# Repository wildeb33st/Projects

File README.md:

# Projects
Repository for Smaller Projects that are not specific to a singular field

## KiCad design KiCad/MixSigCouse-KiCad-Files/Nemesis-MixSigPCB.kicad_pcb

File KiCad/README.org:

* Mixed Signal Hardware Design
This PCB design is based on the course "Mixed Signal Hardware Design" from FEDEVEL Academy. The design makes use of KiCAD for both schematic and PCB Design.  The following URL contains an overview
of the course :
- https://www.phils-lab.net/courses

* Design Specification
Below are the specifications for the design:
- The Device is powered over USB and as such the overall power requirement is *2.5W* with an current of *500mA* and a voltage of *5V*
- The device will be single channel operating within the general audio frequency range i.e. /20Hz to 20kHz/
- Signal Analysis and Signal Generation will be performed by the device
- The use of a DAC/ADC is required along with an MCU. The bit depth chosen for the design is 12.
- The MCU family is the STM32
- SWD is chosen for debugging purposes

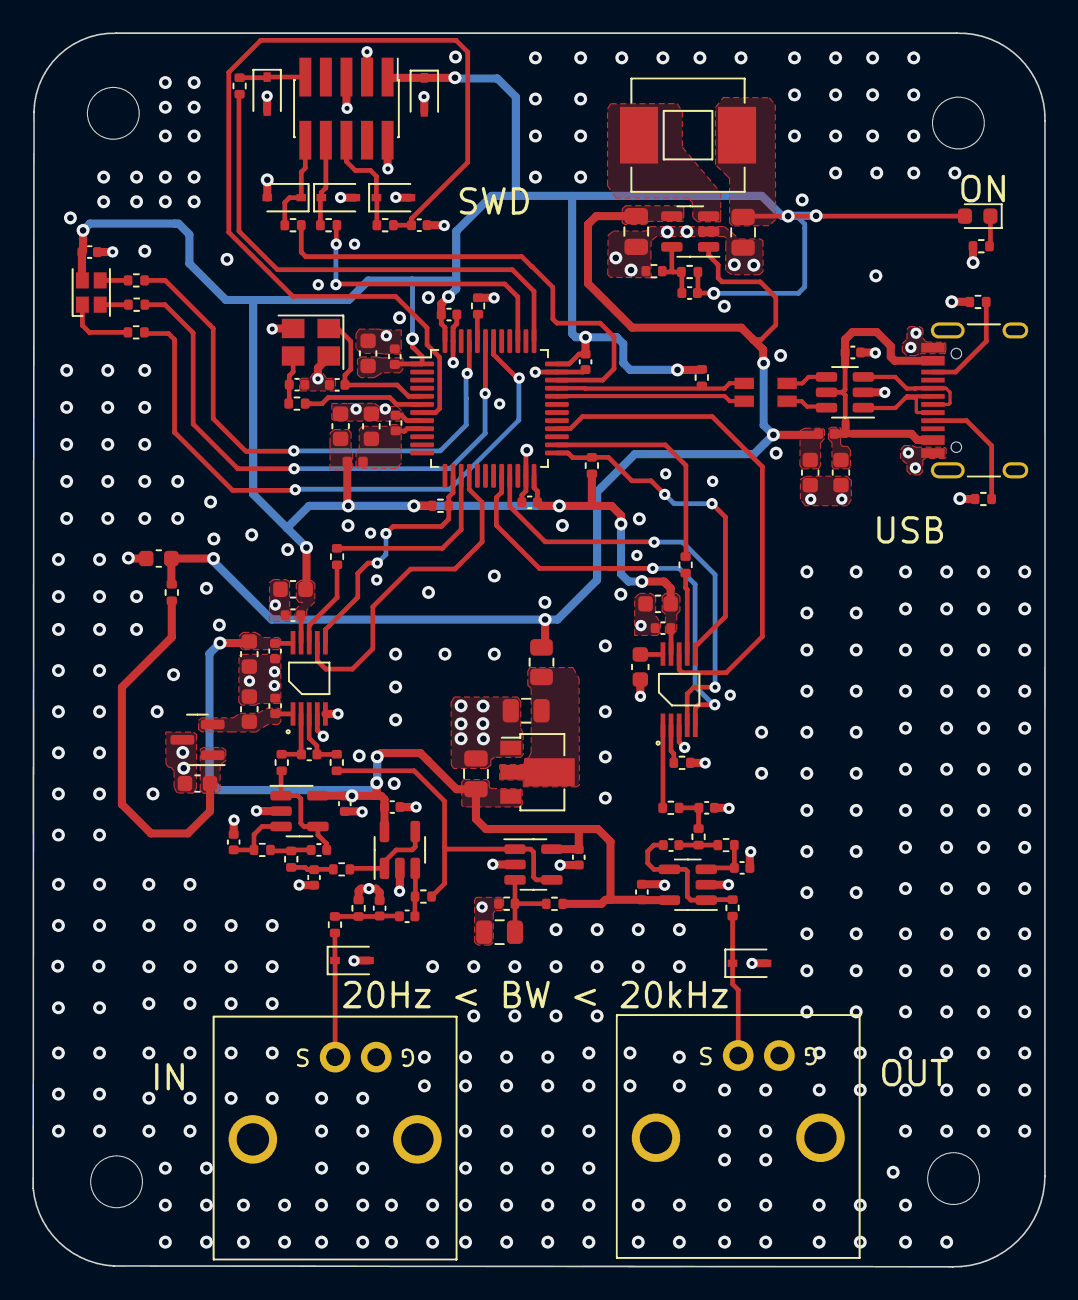
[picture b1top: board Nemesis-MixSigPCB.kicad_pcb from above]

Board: 4 copper layers, 62.5 x 76.2 mm, 114 parts (0 on the bottom side), 68 nets.

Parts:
C100, C101, C206, C207, C402: 1u; C_0603_1608Metric
C102, C103, C104, C105, C107: 22u; C_0805_2012Metric
C106: DNP; C_0402_1005Metric
C108, C201, C202, C203, C204, C210, C211, C212, C301, C302, C306, C311, C313, C314, C401, C406: 100n; C_0402_1005Metric
C200, C308, C309, C310, C312, C315, C400: 10u; C_0603_1608Metric
C205: 10n; C_0402_1005Metric
C208, C209: 10p; C_0402_1005Metric
C300, C304, C307, C404: 150p; C_0402_1005Metric
C303, C305, C403, C405: 1n; C_0402_1005Metric
D100: GREEN; LED_0603_1608Metric
D200: LED_RGB_E6C1206RGBC3UDA; LED_Cree-PLCC4_2x2mm_CW
D201, D202, D203, D204, D205, D300, D400: PESD3V3L1BA,115; D_SOD-323
H1, H2, H3, H4: MountingHole; MountingHole_3.2mm_M3
J200: USB_C_Receptacle_USB2.0; USB_C_Receptacle_HRO_TYPE-C-31-M-12
J201: 2x5 1.27mm; PinHeader_2x05_P1.27mm_Vertical_SMD
J300, J400: 031-5640-1010; AMPHENOL-BNC-031-5640-1010
L100, L200: 10n; L_0402_1005Metric
L101: 15u; MWSA0603S
L201: CMF3216F-900-2P-T; CMC-1206
R100: 10R; R_0805_2012Metric
R101: 100k; R_0402_1005Metric
R102, R304, R403: 22k; R_0402_1005Metric
R103, R104, R105, R207, R208, R209, R300, R306, R307: 1k; R_0402_1005Metric
R200, R202, R203, R401: 10k; R_0402_1005Metric
R201, R309, R400: 0R; R_0402_1005Metric
R204: 1k5; R_0402_1005Metric
R205, R206: 5k1; R_0402_1005Metric
R210, R211, R212, R213, R308, R405: 49R9; R_0402_1005Metric
R301, R302: 2M2; R_0402_1005Metric
R303, R402: 6k8; R_0402_1005Metric
R305, R404: 12k; R_0402_1005Metric
U100: HT7533-1; SOT-89-3
U101: TLV62569DBV; SOT-23-5
U102, U300, U301, U401: MCP6001T-E/OT; SOT-23-5
U200: STM32F103CBT6; LQFP-48_7x7mm_P0.5mm
U201: USBLC6-2SC6; SOT-23-6
U302: REF3033AIDBZT; SOT-23
U303: ADC141S626CIMM_NOPB; VSSOP-10
U400: DAC7563SDGSR; VSSOP-10
Y200: 16MHz; Crystal_SMD_3225-4Pin_3.2x2.5mm

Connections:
+3.3VA: C103.1, C108.1, C302.1, C306.1, C312.1, C313.1, C406.1, R104.2, U100.3 (VOUT), U102.5 (V+), U300.5 (V+), U301.5 (V+), U303.10 (VA), U401.5 (V+)
+3V3: C105.1, C106.1, C200.1, C201.1, C202.1, C203.1, C204.1, C207.1, C211.1, C314.1, C315.1, C400.1, C401.1, D100.2 (A), D200.2, D201.1 (A1), J201.1, L101.2, L200.2, R101.2, R202.1, R203.1, R204.1, U200.1 (VBAT), U200.24 (VDD), U200.36 (VDD), U200.48 (VDD), U303.9 (VIO), U400.9 (AVDD)
+5V: C101.1, C104.1, C308.1, L100.2, R100.2, R308.2, U101.1 (EN), U101.4 (VIN)
/ADC/ADC_IN+: C307.1, R306.1, U303.2 (+IN)
/ADC/ADC_IN-: C307.2, R307.1, U303.3 (-IN)
/ADC/ADC_SCLK: R309.2, U303.8 (SCLK)
/ADC/ADC_VREF: C310.1, C311.1, U302.2 (OUT), U303.1 (VREF)
/ADC/ADC_VREF_VIN: C309.1, R308.1, U302.1 (IN)
/ADC/IN: D300.1 (A1), J300.1 (In), R300.2
/ADC/IN_AA_BUF_IN: C304.1, R305.1, U301.3 (+)
/ADC/IN_AA_BUF_OUT: C305.2, R306.2, U301.1, U301.4 (-)
/ADC/IN_BUF: C301.1, R302.1, U300.3 (+)
/ADC/IN_BUF_OUT: R303.2, U300.1, U300.4 (-)
/ADC/IN_RF: C300.1, C301.2, R300.1, R301.2
/DAC/DAC_OUT_A: R402.2, U400.1 (VOUT_A)
/DAC/DAC_OUT_B: R401.1, U400.2 (VOUT_B)
/DAC/DAC_SCLK: R400.2, U400.7 (SCLK)
/DAC/DAC_VREF: C402.1, U400.10 (VREFIN/VREFOUT)
/DAC/OUT: D400.1 (A1), J400.1 (In), R405.1
/DAC/OUT_AA_BUF_IN: C404.1, R404.1, U401.3 (+)
/DAC/OUT_AA_BUF_OUT: C405.2, R405.2, U401.1, U401.4 (-)
/MCU/BOOT0: R200.1, U200.44 (BOOT0)
/MCU/CONN_NRST: D205.1 (A1), J201.6, R213.2
/MCU/CONN_SWCLK: D203.1 (A1), J201.9, R211.2
/MCU/CONN_SWDIO: D202.1 (A1), J201.10, R210.2
/MCU/CONN_SWO: D204.1 (A1), J201.8, R212.2
/MCU/HSE_IN: C208.1, U200.5 (PD0), Y200.1
/MCU/HSE_OUT: R201.1, U200.6 (PD1)
/MCU/LED_B_K: D200.4, R209.2
/MCU/LED_G_K: D200.1, R208.2
/MCU/LED_R_K: D200.3, R207.2
/MCU/NRST: C212.1, R213.1, U200.7 (NRST)
/MCU/SWCLK: R211.1, U200.37 (PA14)
/MCU/SWDIO: R210.1, U200.34 (PA13)
/MCU/SWO: R212.1, U200.39 (PB3)
/MCU/TIM4_CH1: R208.1, U200.42 (PB6)
/MCU/TIM4_CH2: R209.1, U200.43 (PB7)
/MCU/TIM4_CH3: R207.1, U200.45 (PB8)
/MCU/USB_CMC_D+: L201.2, U201.4 (I/O2)
/MCU/USB_CMC_D-: L201.1, U201.6 (I/O1)
/MCU/USB_CONN_CC1: J200.A5 (CC1), R205.1
/MCU/USB_CONN_CC2: J200.B5 (CC2), R206.1
/MCU/USB_CONN_D+: J200.A6 (D+), J200.B6 (D+), U201.3 (I/O2)
/MCU/USB_CONN_D-: J200.A7 (D-), J200.B7 (D-), U201.1 (I/O1)
/MCU/USB_D+: L201.3, R204.2, U200.33 (PA12)
/MCU/USB_D-: L201.4, U200.32 (PA11)
/MCU/XTAL_IN: C209.1, R201.2, Y200.3
/Power/+5V_FILT: C102.1, R100.1, U100.2 (VIN)
/Power/BUCK_FB: C106.2, R101.1, R102.2, U101.5 (FB)
/Power/BUCK_SW: L101.1, U101.3 (SW)
/Power/LED_PWR_K: D100.1 (K), R103.2
/Power/VREF: C107.1, R104.1, R105.2, U102.3 (+)
DAC_NCLR: U200.20 (PB2), U400.5 (NCLR)
DAC_NLDAC: U200.21 (PB10), U400.4 (NLDAC)
GND: C100.2, C101.2, C102.2, C103.2, C104.2, C105.2, C107.2, C108.2, C200.2, C201.2, C202.2, C203.2, C204.2, C205.2, C206.2, C207.2, C208.2, C209.2, C210.2, C211.2, C212.2, C300.2, C302.2, C303.2, C304.2, C306.2, C308.2, C309.2, C310.2, C311.2, C312.2, C313.2, C314.2, C315.2, C400.2, C401.2, C402.2, C403.2, C404.2, C406.2, D201.2 (A2), D202.2 (A2), D203.2 (A2), D204.2 (A2), D205.2 (A2), D300.2 (A2), D400.2 (A2), J200.A1 (GND), J200.A12 (GND), J200.B1 (GND), J200.B12 (GND), J200.S1 (SHIELD), J201.2, J201.3, J201.5, J300.2 (Ext), J400.2 (Ext), R102.1, R103.1, R105.1, R200.2, R205.2, R206.2, R301.1, R401.2, U100.1 (GND), U101.2 (GND), U102.2 (V-), U200.8 (VSSA), U200.23 (VSS), U200.35 (VSS), U200.47 (VSS), U201.2 (GND), U300.2 (V-), U301.2 (V-), U302.3 (GND), U303.4 (GND), U303.5 (GND), U400.3 (GND), U401.2 (V-), Y200.2, Y200.4
unnamed: C303.1, R303.1, R304.2
unnamed: C305.1, R304.1, R305.2
unnamed: C403.1, R402.1, R403.2
unnamed: C405.1, R403.1, R404.2
SPI1_MISO: U200.16 (PA6), U303.7 (DOUT)
SPI1_NSS: R203.2, U200.14 (PA4), U303.6 (NCS)
SPI1_SCK: R309.1, U200.15 (PA5)
SPI2_MOSI: U200.28 (PB15), U400.8 (DIN)
SPI2_NSS: R202.2, U200.25 (PB12), U400.6 (NSYNC)
SPI2_SCK: R400.1, U200.26 (PB13)
VBUS: C100.1, C210.1, J200.A4 (VBUS), J200.A9 (VBUS), J200.B4 (VBUS), J200.B9 (VBUS), L100.1, U201.5 (VBUS)
VCOM: R302.2, R307.2, U102.1, U102.4 (-)
VDDA: C205.1, C206.1, L200.1, U200.9 (VDDA)

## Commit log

2022-02-07 Adding Moving Average Filter Project
2022-02-07 Adding README for further project description
2022-02-07 folder cleanup
2022-02-07 updated FIR Filter
2022-02-08 Image Processing project
2022-02-08 Embedded C for Atmega328p MCU
2022-11-30 KiCad project added
2022-12-28 Changes to the Structure
2022-12-28 Mixed Signal Design Course Added
2022-12-28 File Structure Change
